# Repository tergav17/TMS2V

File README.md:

# TMS2V
This project aims to allow a V9938 VDP to be installed in place of a TMS9918A. Since the V9938 is (largely) backwards compatible with the TMS9918A, existing software for upgraded systems should still function as normal. 
Besides interposing the 40-pin socket that the TMS9918A plugged into, an extra address line may be attacked to the bus to allow for addressing of the addition 2 ports found on the V9938.

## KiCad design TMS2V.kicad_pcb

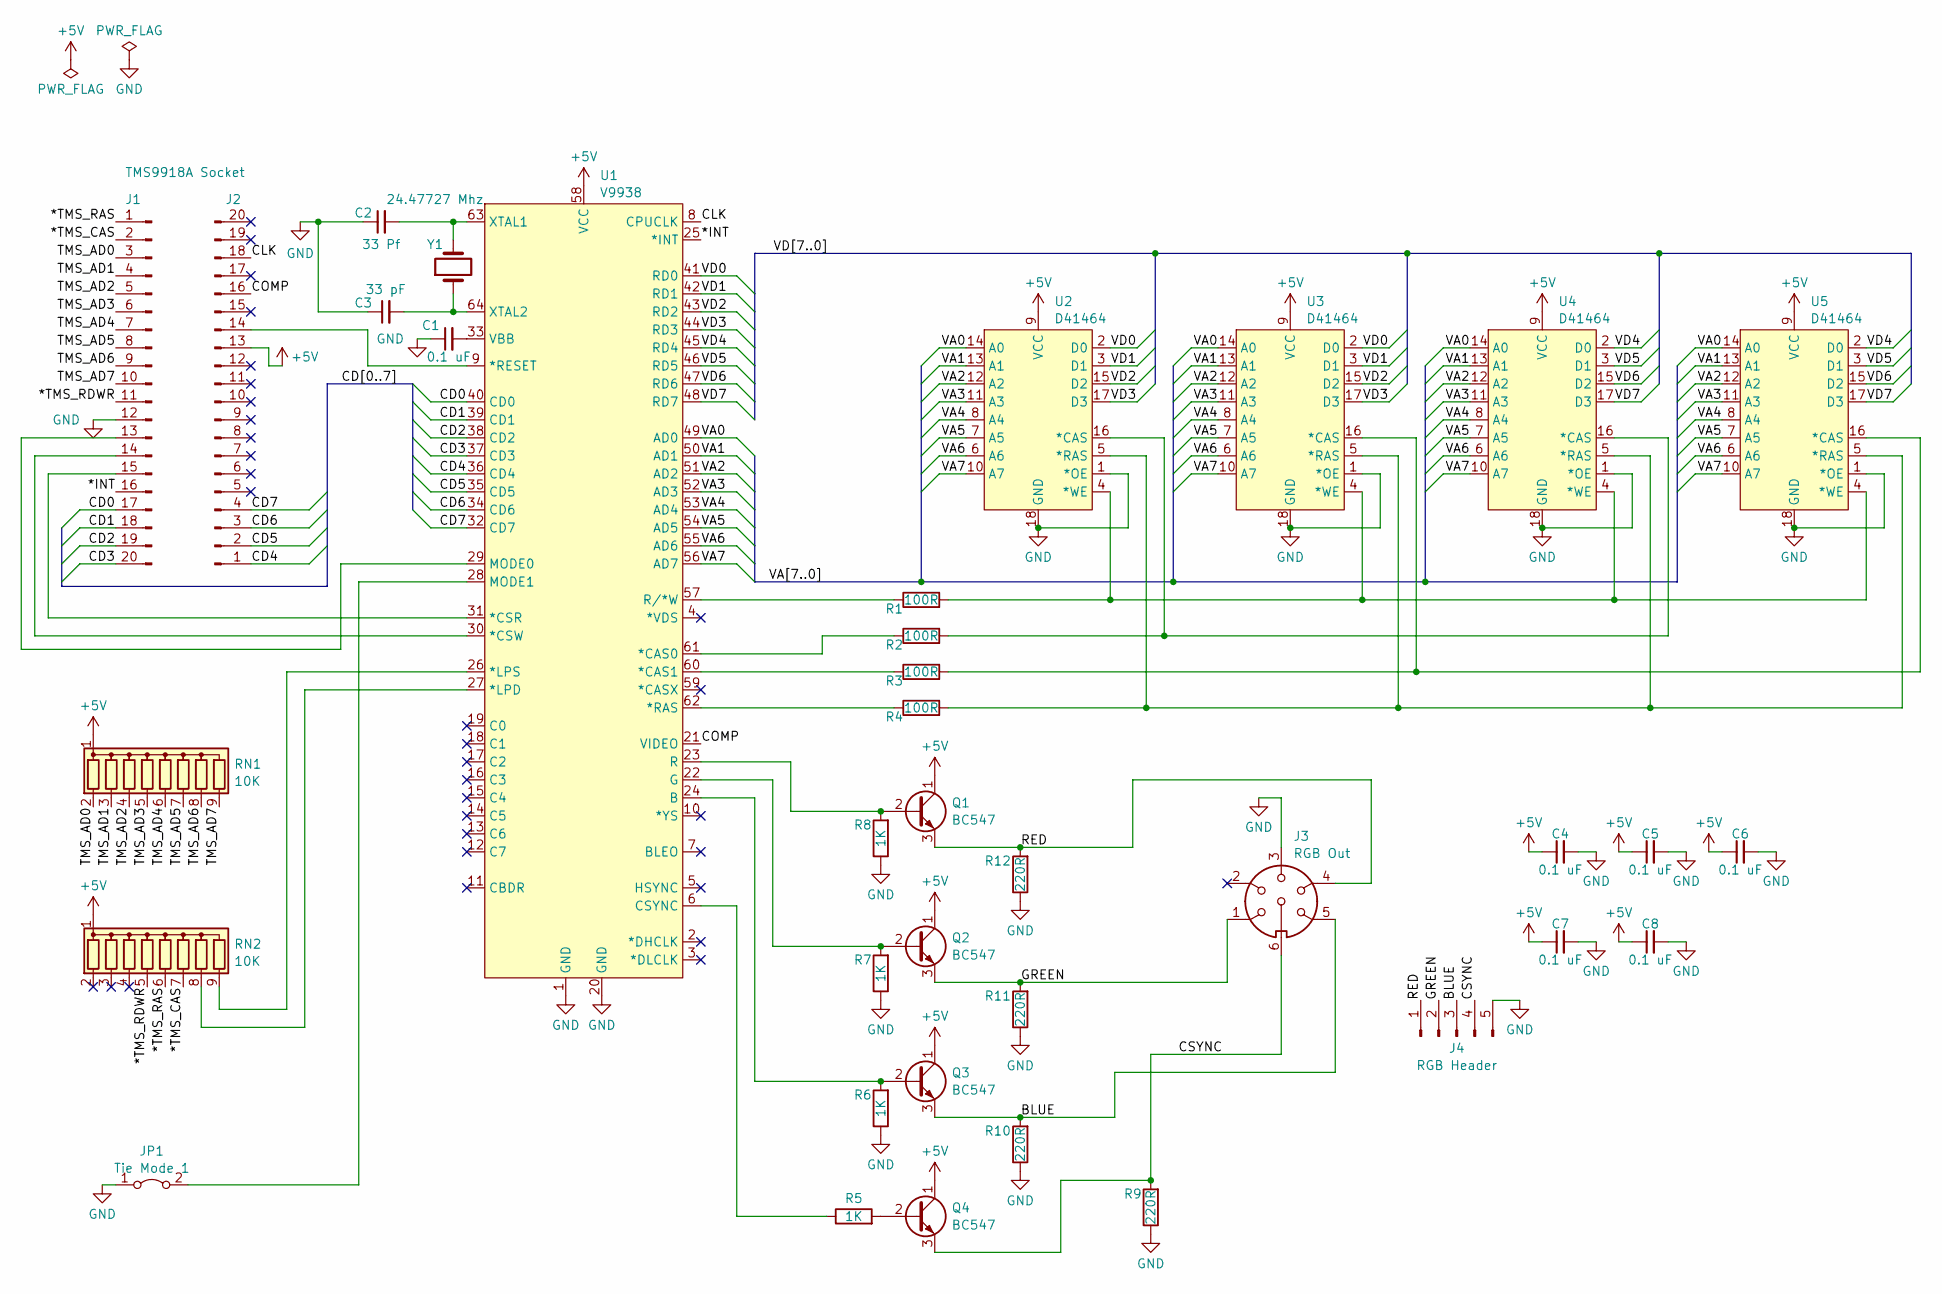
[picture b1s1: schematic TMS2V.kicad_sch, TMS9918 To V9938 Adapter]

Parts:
C1, C4, C5, C6, C7, C8: 0.1 uF; C_Disc_D5.0mm_W2.5mm_P5.00mm
C2: 33 Pf; C_Disc_D5.0mm_W2.5mm_P5.00mm
C3: 33 pF; C_Disc_D5.0mm_W2.5mm_P5.00mm
J1: TMS9918A Socket; PinHeader_1x20_P2.54mm_Vertical
J2: PinHeader_1x20_P2.54mm_Vertical
J3: RGB Out; DIN-6
J4: RGB Header; PinHeader_1x05_P2.54mm_Vertical
JP1: Tie Mode 1; PinHeader_1x02_P2.54mm_Vertical
Q1, Q2, Q3, Q4: BC547; TO-92_Inline
R1, R2, R3, R4: 100R; R_Axial_DIN0207_L6.3mm_D2.5mm_P7.62mm_Horizontal
R5, R6, R7, R8: 1K; R_Axial_DIN0207_L6.3mm_D2.5mm_P7.62mm_Horizontal
R9, R10, R11, R12: 220R; R_Axial_DIN0207_L6.3mm_D2.5mm_P7.62mm_Horizontal
RN1, RN2: 10K; R_Array_SIP9
U1: V9938; DIP64
U2, U3, U4, U5: D41464; DIP-18_W7.62mm
Y1: 24.47727 Mhz; Crystal_HC49-U_Vertical

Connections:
+5V: C4.1, C5.1, C6.1, C7.1, C8.1, J2.13, Q1.1 (C), Q2.1 (C), Q3.1 (C), Q4.1 (C), RN1.1 (common), RN2.1 (common), U1.58 (VCC), U2.9 (VCC), U3.9 (VCC), U4.9 (VCC), U5.9 (VCC)
/*INT: J1.16, U1.25 (*INT)
/*TMS_CAS: J1.2, RN2.7 (R6)
/*TMS_RAS: J1.1, RN2.6 (R5)
/*TMS_RDWR: J1.11, RN2.5 (R4)
/BLUE: J3.5, J4.3, Q3.3 (E), R10.2
/CD0: J1.17, U1.40 (CD0)
/CD1: J1.18, U1.39 (CD1)
/CD2: J1.19, U1.38 (CD2)
/CD3: J1.20, U1.37 (CD3)
/CD4: J2.1, U1.36 (CD4)
/CD5: J2.2, U1.35 (CD5)
/CD6: J2.3, U1.34 (CD6)
/CD7: J2.4, U1.32 (CD7)
/CLK: J2.18, U1.8 (CPUCLK)
/COMP: J2.16, U1.21 (VIDEO)
/CSYNC: J3.6, J4.4, Q4.3 (E), R9.2
/GREEN: J3.1, J4.2, Q2.3 (E), R11.2
/RED: J3.4, J4.1, Q1.3 (E), R12.2
/TMS_AD0: J1.3, RN1.2 (R1)
/TMS_AD1: J1.4, RN1.3 (R2)
/TMS_AD2: J1.5, RN1.4 (R3)
/TMS_AD3: J1.6, RN1.5 (R4)
/TMS_AD4: J1.7, RN1.6 (R5)
/TMS_AD5: J1.8, RN1.7 (R6)
/TMS_AD6: J1.9, RN1.8 (R7)
/TMS_AD7: J1.10, RN1.9 (R8)
/VA0: U1.49 (AD0), U2.14 (A0), U3.14 (A0), U4.14 (A0), U5.14 (A0)
/VA1: U1.50 (AD1), U2.13 (A1), U3.13 (A1), U4.13 (A1), U5.13 (A1)
/VA2: U1.51 (AD2), U2.12 (A2), U3.12 (A2), U4.12 (A2), U5.12 (A2)
/VA3: U1.52 (AD3), U2.11 (A3), U3.11 (A3), U4.11 (A3), U5.11 (A3)
/VA4: U1.53 (AD4), U2.8 (A4), U3.8 (A4), U4.8 (A4), U5.8 (A4)
/VA5: U1.54 (AD5), U2.7 (A5), U3.7 (A5), U4.7 (A5), U5.7 (A5)
/VA6: U1.55 (AD6), U2.6 (A6), U3.6 (A6), U4.6 (A6), U5.6 (A6)
/VA7: U1.56 (AD7), U2.10 (A7), U3.10 (A7), U4.10 (A7), U5.10 (A7)
/VD0: U1.41 (RD0), U2.2 (D0), U3.2 (D0)
/VD1: U1.42 (RD1), U2.3 (D1), U3.3 (D1)
/VD2: U1.43 (RD2), U2.15 (D2), U3.15 (D2)
/VD3: U1.44 (RD3), U2.17 (D3), U3.17 (D3)
/VD4: U1.45 (RD4), U4.2 (D0), U5.2 (D0)
/VD5: U1.46 (RD5), U4.3 (D1), U5.3 (D1)
/VD6: U1.47 (RD6), U4.15 (D2), U5.15 (D2)
/VD7: U1.48 (RD7), U4.17 (D3), U5.17 (D3)
GND: C1.1, C2.1, C3.1, C4.2, C5.2, C6.2, C7.2, C8.2, J1.12, J3.3, J4.5, JP1.1 (A), R6.1, R7.1, R8.1, R9.1, R10.1, R11.1, R12.1, U1.1 (GND), U1.20 (GND), U2.1 (*OE), U2.18 (GND), U3.1 (*OE), U3.18 (GND), U4.1 (*OE), U4.18 (GND), U5.1 (*OE), U5.18 (GND)
unnamed: J1.13, U1.29 (MODE0)
unnamed: J1.14, U1.30 (*CSW)
unnamed: J1.15, U1.31 (*CSR)
unnamed: J2.14, U1.9 (*RESET)
unnamed: JP1.2 (B), U1.28 (MODE1)
unnamed: Q1.2 (B), R8.2, U1.23 (R)
unnamed: Q2.2 (B), R7.2, U1.22 (G)
unnamed: Q3.2 (B), R6.2, U1.24 (B)
unnamed: Q4.2 (B), R5.2
unnamed: RN2.8 (R7), U1.27 (*LPD)
unnamed: RN2.9 (R8), U1.26 (*LPS)
unnamed: R2.1, U1.61 (*CAS0)
unnamed: R3.1, U1.60 (*CAS1)
unnamed: R4.1, U1.62 (*RAS)
unnamed: R5.1, U1.6 (CSYNC)
unnamed: R1.1, U1.57 (R/*W)
unnamed: C1.2, U1.33 (VBB)
unnamed: C2.2, U1.63 (XTAL1), Y1.2
unnamed: C3.2, U1.64 (XTAL2), Y1.1
unnamed: R2.2, U2.16 (*CAS), U4.16 (*CAS)
unnamed: R4.2, U2.5 (*RAS), U3.5 (*RAS), U4.5 (*RAS), U5.5 (*RAS)
unnamed: R1.2, U2.4 (*WE), U3.4 (*WE), U4.4 (*WE), U5.4 (*WE)
unnamed: R3.2, U3.16 (*CAS), U5.16 (*CAS)

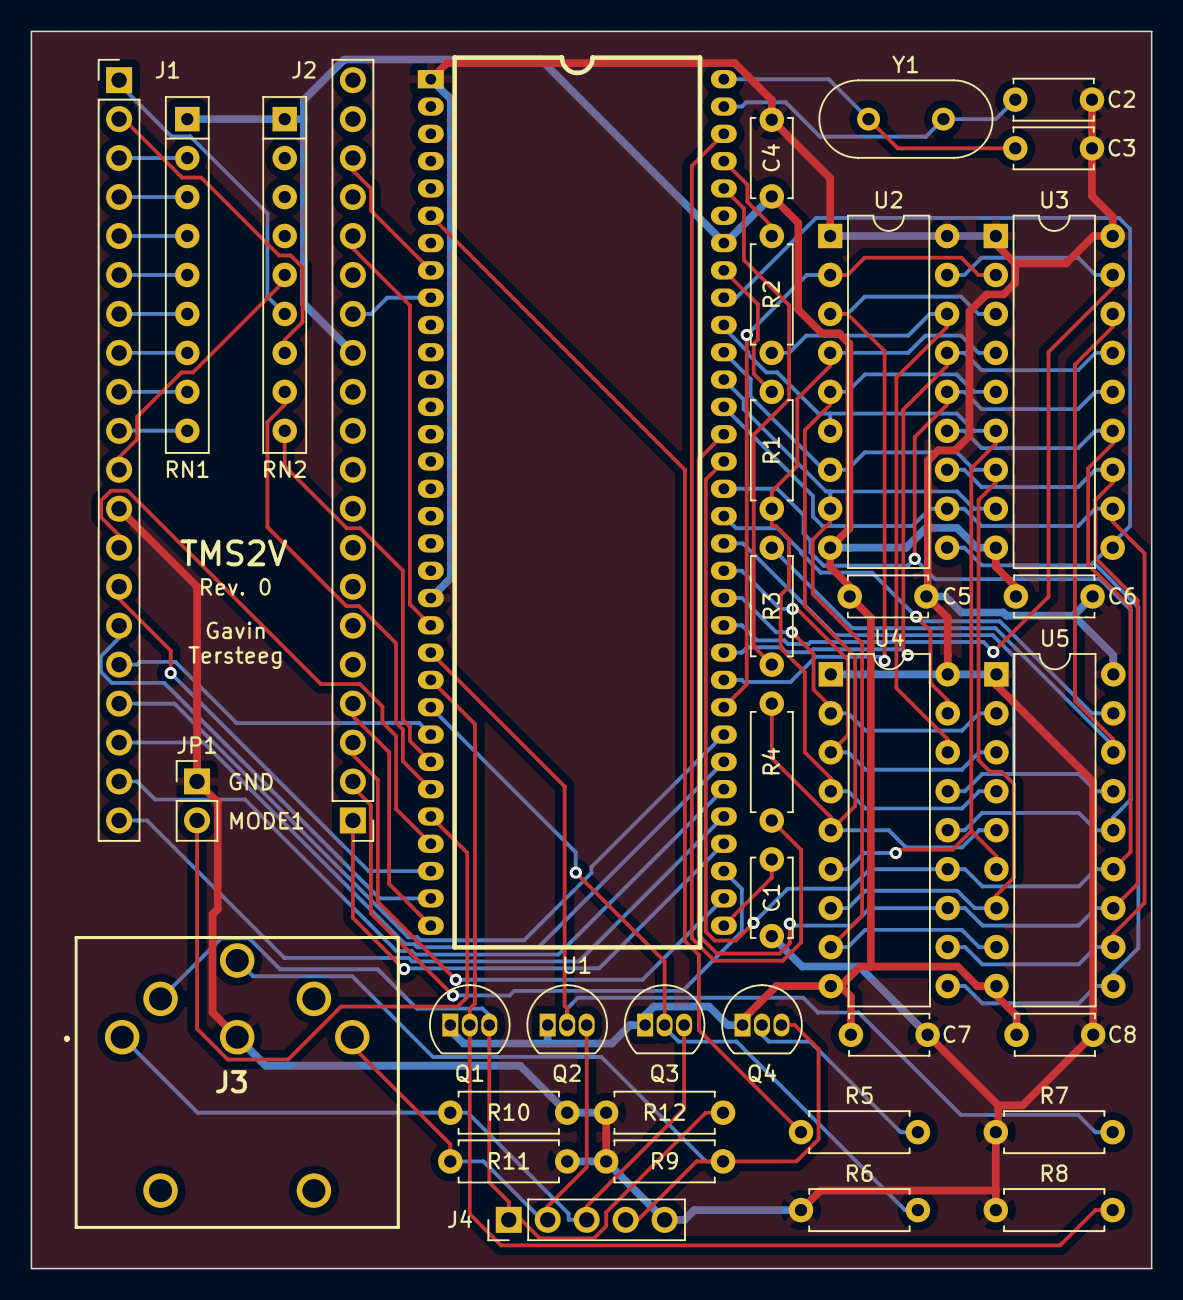
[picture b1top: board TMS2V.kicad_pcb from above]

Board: 2 copper layers, 73.0 x 80.6 mm, 37 parts (0 on the bottom side), 67 nets.

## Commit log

2024-08-01 Added D41464 footprint and logic
2024-08-02 TMS9918A hookup
2024-08-04 oscillator circuit
2024-08-05 Started work on video output circuit
2024-08-06 Started work on PCB layout
2024-08-07 Initial PCB layout
2024-08-07 Generated gerbers
